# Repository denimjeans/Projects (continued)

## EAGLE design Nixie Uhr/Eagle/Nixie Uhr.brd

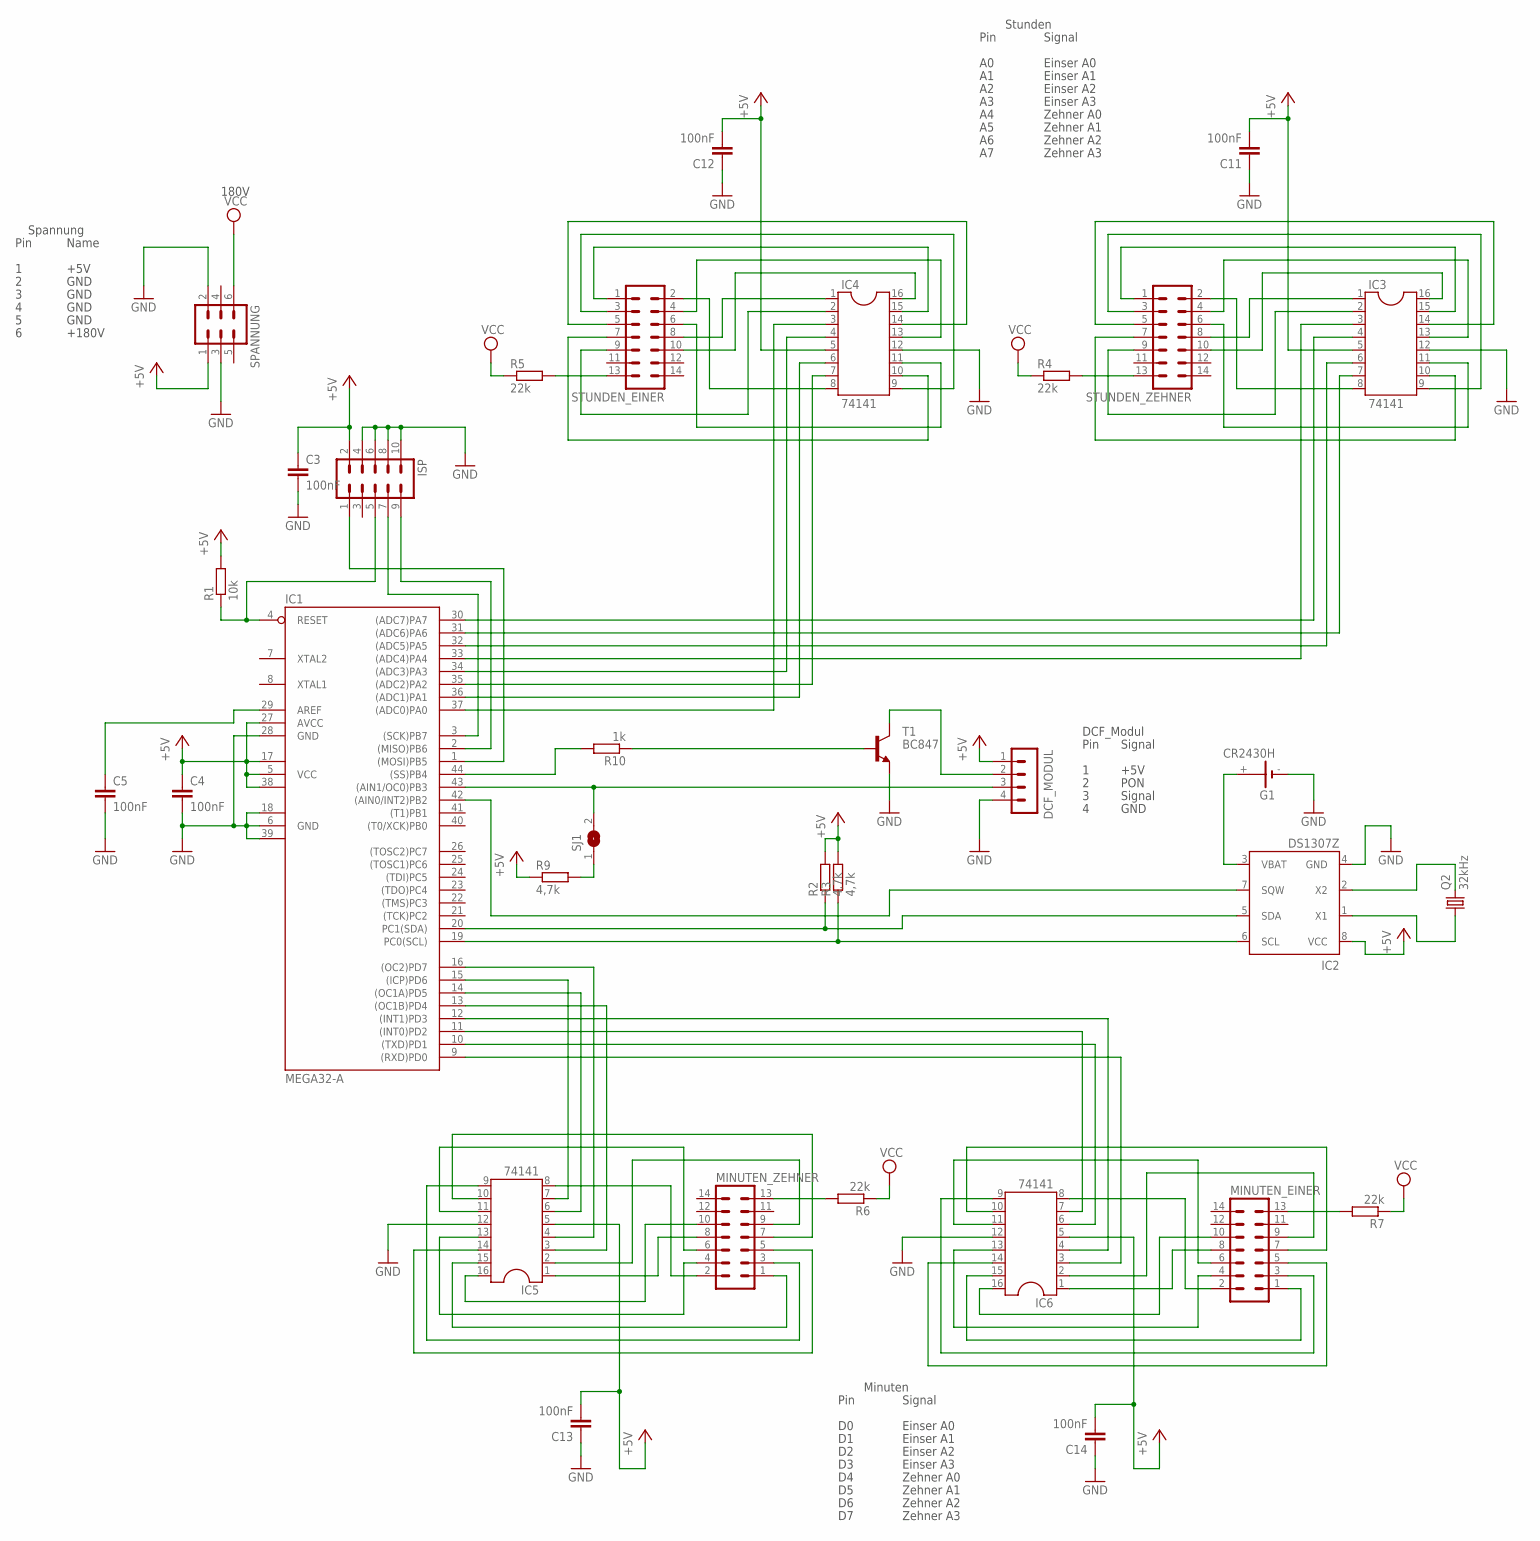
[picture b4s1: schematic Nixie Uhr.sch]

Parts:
C3, C4, C5, C11, C12, C13, C14: 100nF; C0805
DCF_MODUL: MA04-1
G1: CR2430H
IC1: MEGA32-A; TQFP44
IC2: DS1307Z; SOIC8
IC3, IC4, IC5, IC6: 74141; DIL16
ISP: ML10
MINUTEN_EINER: ML14
MINUTEN_ZEHNER: ML14
Q2: 32kHz; TC26V
R1: 10k; R0805
R2, R3, R9: 4,7k; R0805
R4, R5, R6, R7: 22k; 0204/7
R10: 1k; R0805
SJ1: SJ
SPANNUNG: ML6
STUNDEN_EINER: ML14
STUNDEN_ZEHNER: ML14
T1: BC847; SOT23

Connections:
+5V: C3.1, C4.1, C11.2, C12.2, C13.2, C14.2, DCF_MODUL.1, IC1.5 (VCC), IC1.17 (VCC1), IC1.27 (AVCC), IC1.38 (VCC2), IC2.8 (VCC), IC3.5, IC4.5, IC5.5, IC6.5, ISP.2, R1.2, R2.2, R3.2, R9.1, SPANNUNG.1
DCF_SIGNAL: DCF_MODUL.3, IC1.43 ((AIN1/OC0)PB3), SJ1.2
GND: C3.2, C4.2, C5.2, C11.1, C12.1, C13.1, C14.1, DCF_MODUL.4, G1.-, IC1.6 (GND), IC1.18 (GND1), IC1.28 (GND), IC1.39 (GND2), IC2.4 (GND), IC3.12, IC4.12, IC5.12, IC6.12, ISP.4, ISP.6, ISP.8, ISP.10, SPANNUNG.2, SPANNUNG.3, T1.2 (E)
MINUTEN_EINSER_A0: IC1.9 ((RXD)PD0), IC6.3
MINUTEN_MINUTEN_A1: IC1.10 ((TXD)PD1), IC6.6
MINUTEN_MINUTEN_A2: IC1.11 ((INT0)PD2), IC6.7
MINUTEN_MINUTEN_A3: IC1.12 ((INT1)PD3), IC6.4
MINUTEN_ZEHNER_A0: IC1.13 ((OC1B)PD4), IC5.3
MINUTEN_ZEHNER_A1: IC1.14 ((OC1A)PD5), IC5.6
MINUTEN_ZEHNER_A2: IC1.15 ((ICP)PD6), IC5.7
MINUTEN_ZEHNER_A3: IC1.16 ((OC2)PD7), IC5.4
MISO: IC1.2 ((MISO)PB6), ISP.9
MOSI: IC1.1 ((MOSI)PB5), ISP.1
unnamed: IC3.15, STUNDEN_ZEHNER.1
unnamed: R4.2, STUNDEN_ZEHNER.13
unnamed: G1.+, IC2.3 (VBAT)
unnamed: IC1.42 ((AIN0/INT2)PB2), IC2.7 (SQW)
unnamed: IC2.2 (X2), Q2.2
unnamed: IC3.9, STUNDEN_ZEHNER.3
unnamed: IC3.8, STUNDEN_ZEHNER.2
unnamed: IC3.13, STUNDEN_ZEHNER.4
unnamed: IC3.14, STUNDEN_ZEHNER.5
unnamed: IC3.11, STUNDEN_ZEHNER.6
unnamed: IC3.10, STUNDEN_ZEHNER.7
unnamed: IC3.1, STUNDEN_ZEHNER.8
unnamed: IC3.2, STUNDEN_ZEHNER.9
unnamed: IC3.16, STUNDEN_ZEHNER.10
unnamed: R5.2, STUNDEN_EINER.13
unnamed: R9.2, SJ1.1
unnamed: IC1.44 ((SS)PB4), R10.2
unnamed: IC4.15, STUNDEN_EINER.1
unnamed: IC4.9, STUNDEN_EINER.3
unnamed: IC4.8, STUNDEN_EINER.2
unnamed: IC4.13, STUNDEN_EINER.4
unnamed: IC4.14, STUNDEN_EINER.5
unnamed: IC4.11, STUNDEN_EINER.6
unnamed: IC4.10, STUNDEN_EINER.7
unnamed: IC4.1, STUNDEN_EINER.8
unnamed: IC4.2, STUNDEN_EINER.9
unnamed: IC4.16, STUNDEN_EINER.10
unnamed: R10.1, T1.1 (B)
unnamed: C5.1, IC1.29 (AREF)
unnamed: DCF_MODUL.2, T1.3 (C)
unnamed: MINUTEN_ZEHNER.13, R6.2
unnamed: IC5.15, MINUTEN_ZEHNER.1
unnamed: IC5.9, MINUTEN_ZEHNER.3
unnamed: IC5.8, MINUTEN_ZEHNER.2
unnamed: IC5.13, MINUTEN_ZEHNER.4
unnamed: IC5.14, MINUTEN_ZEHNER.5
unnamed: IC5.11, MINUTEN_ZEHNER.6
unnamed: IC5.10, MINUTEN_ZEHNER.7
unnamed: IC5.1, MINUTEN_ZEHNER.8
unnamed: IC5.2, MINUTEN_ZEHNER.9
unnamed: IC5.16, MINUTEN_ZEHNER.10
unnamed: MINUTEN_EINER.13, R7.2
unnamed: IC6.15, MINUTEN_EINER.1
unnamed: IC6.9, MINUTEN_EINER.3
unnamed: IC6.8, MINUTEN_EINER.2
unnamed: IC6.13, MINUTEN_EINER.4
unnamed: IC6.14, MINUTEN_EINER.5
unnamed: IC6.11, MINUTEN_EINER.6
unnamed: IC6.10, MINUTEN_EINER.7
unnamed: IC6.1, MINUTEN_EINER.8
unnamed: IC6.2, MINUTEN_EINER.9
unnamed: IC6.16, MINUTEN_EINER.10
unnamed: IC2.1 (X1), Q2.1
RESET: IC1.4 (RESET), ISP.5, R1.1
SCK: IC1.3 ((SCK)PB7), ISP.7
SCL: IC1.19 (PC0(SCL)), IC2.6 (SCL), R3.1
SDA: IC1.20 (PC1(SDA)), IC2.5 (SDA), R2.1
STUNDEN_EINER_A0: IC1.37 ((ADC0)PA0), IC4.3
STUNDEN_EINER_A1: IC1.36 ((ADC1)PA1), IC4.6
STUNDEN_EINER_A2: IC1.35 ((ADC2)PA2), IC4.7
STUNDEN_EINER_A3: IC1.34 ((ADC3)PA3), IC4.4
STUNDEN_ZEHNER_A0: IC1.33 ((ADC4)PA4), IC3.3
STUNDEN_ZEHNER_A1: IC1.32 ((ADC5)PA5), IC3.6
STUNDEN_ZEHNER_A2: IC1.31 ((ADC6)PA6), IC3.7
STUNDEN_ZEHNER_A3: IC1.30 ((ADC7)PA7), IC3.4
VCC: R4.1, R5.1, R6.1, R7.1, SPANNUNG.6

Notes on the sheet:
Pin
Name
+5V
+180V
GND
180V
Signal
Einser A0
Einser A1
Einser A2
Einser A3
Minuten
Zehner A0
Zehner A1
Zehner A2
Zehner A3
Stunden
PON
DCF_Modul
Spannung

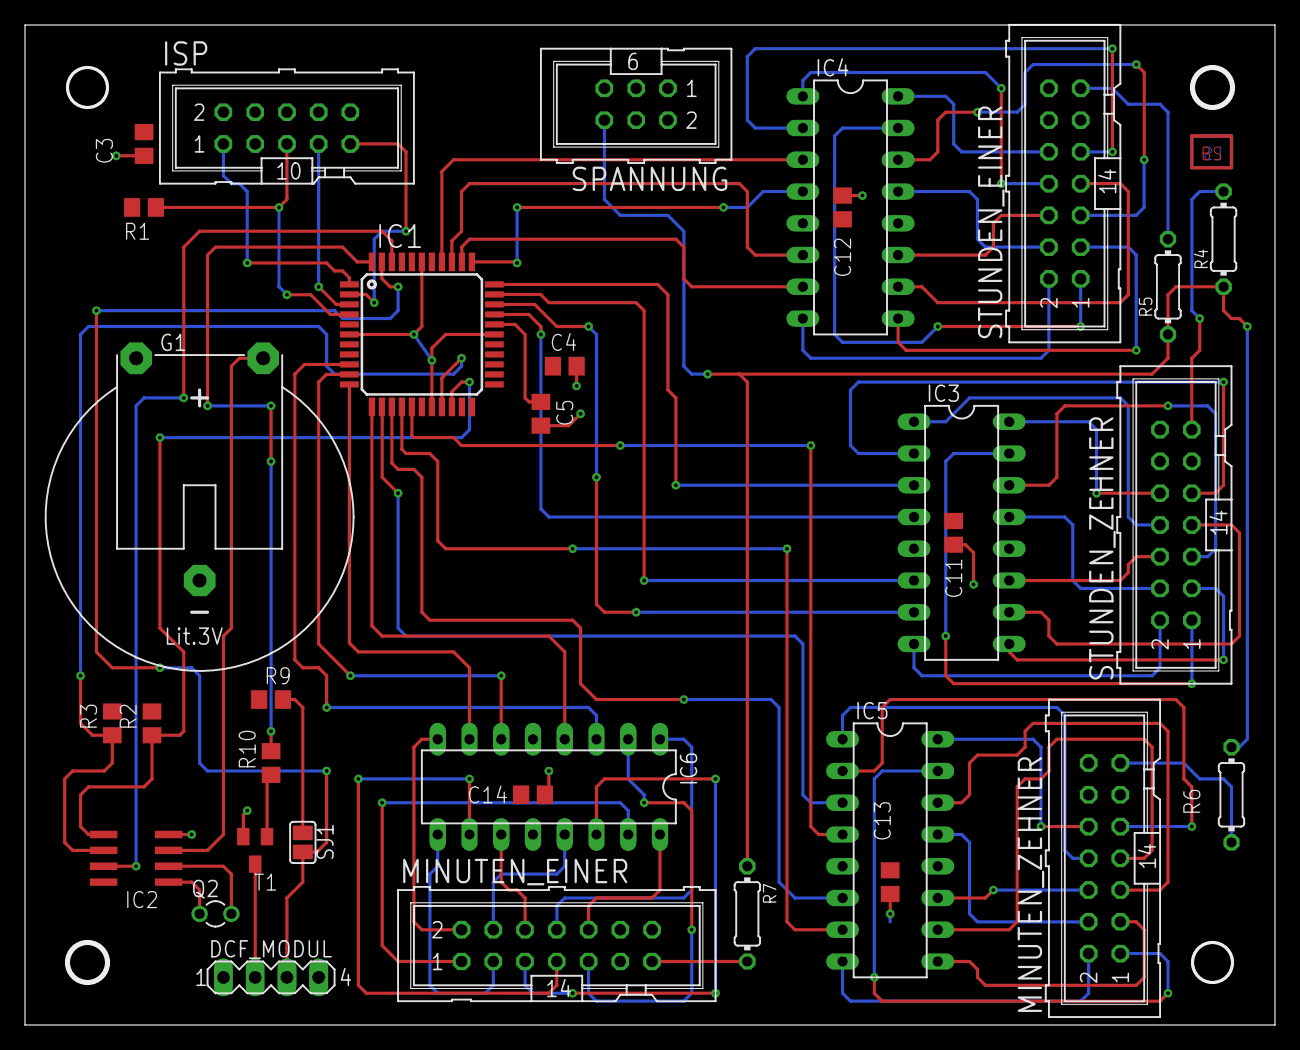
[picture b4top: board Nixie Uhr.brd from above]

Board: 2 copper layers, 99.6 x 79.6 mm, 33 parts (0 on the bottom side), 79 nets.

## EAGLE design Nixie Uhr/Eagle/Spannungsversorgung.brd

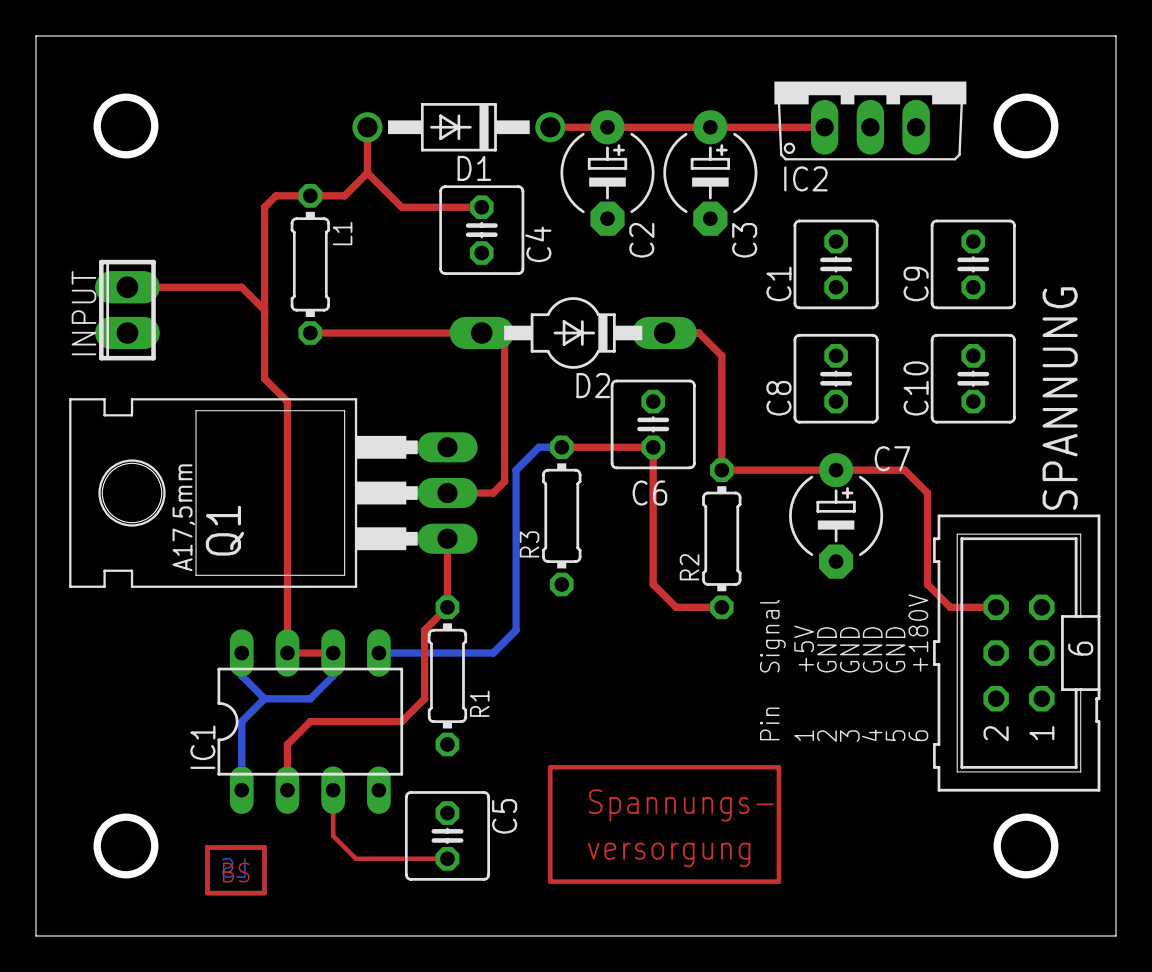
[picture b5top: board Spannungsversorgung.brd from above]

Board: 2 copper layers, 59.6 x 49.6 mm, 21 parts (0 on the bottom side), 9 nets.

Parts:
C1, C4, C6, C8, C9, C10: 100nF; C025-050X050
C2, C3: 100µF; E5-5
C5: 470pF; C025-050X050
C7: 10µF; E5-5
D1: 1N4004; DO41-10
D2: BYV26; SOD57-10
IC1: MC34063; DIL08
IC2: 7805TV; TO220V
INPUT: 2POL254
L1: 330µH; 0204/7
Q1: IRF820; TO220
R1: 150R; 0204/7
R2: 820K; 0204/7
R3: 5k6; 0204/7
SPANNUNG: J1; ML6

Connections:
+5V: C1.1, C8.1, C9.1, C10.1, IC2.3, SPANNUNG.1
+12V: C4.2, D1.A, IC1.1, IC1.6, IC1.7, IC1.8, INPUT.2, L1.1
GND: C1.2, C2.-, C3.-, C4.1, C5.1, C6.2, C7.-, C8.2, C9.2, C10.2, IC1.4, IC2.2, INPUT.1, Q1.3, R1.1, R3.1, SPANNUNG.2, SPANNUNG.3
unnamed: C2.+, C3.+, D1.C, IC2.1
unnamed: D2.A, L1.2, Q1.2
unnamed: C6.1, IC1.5, R2.1, R3.2
unnamed: C5.2, IC1.3
unnamed: IC1.2, Q1.1, R1.2
VCC: C7.+, D2.C, R2.2, SPANNUNG.6

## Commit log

2013-03-02 Uploading Projectfiles
2013-03-02 Deleting Folder "Datasheet", because it´s useless.
